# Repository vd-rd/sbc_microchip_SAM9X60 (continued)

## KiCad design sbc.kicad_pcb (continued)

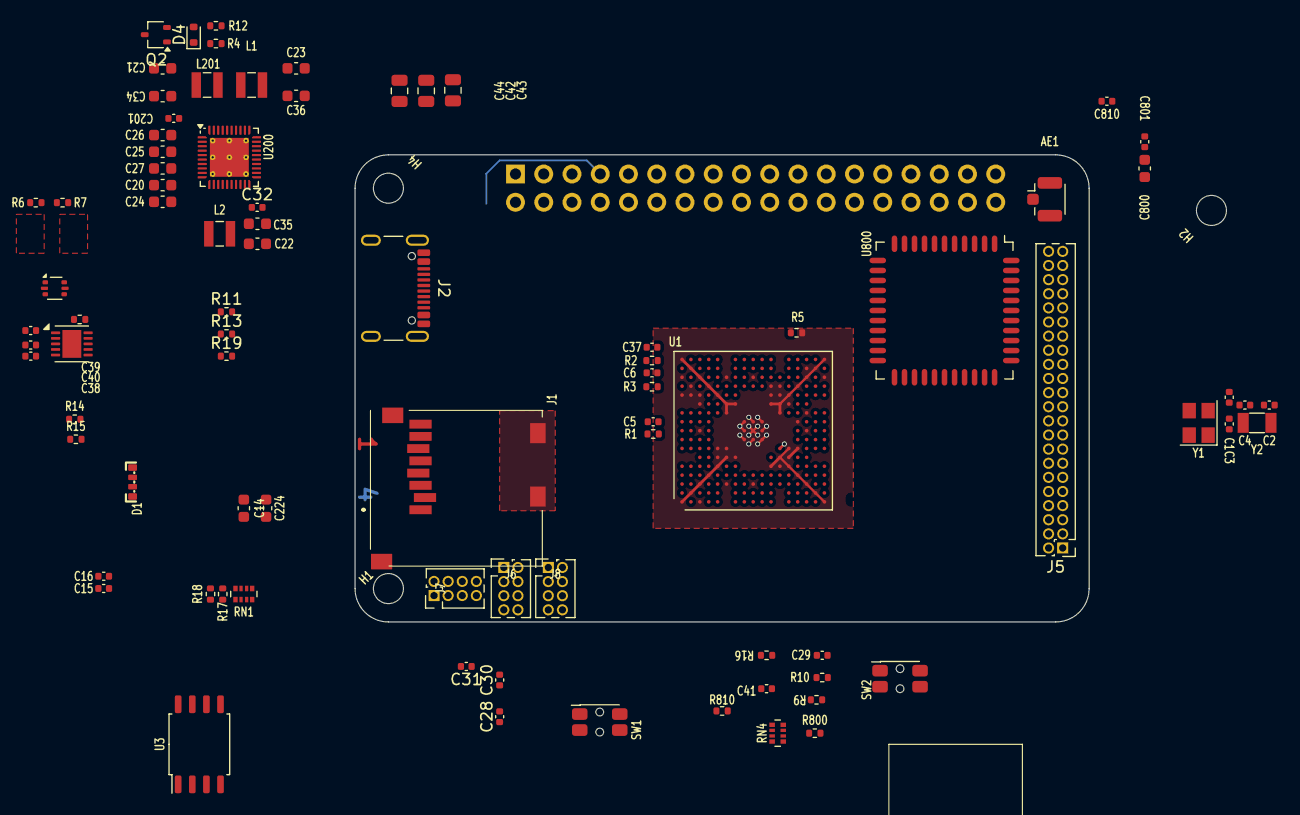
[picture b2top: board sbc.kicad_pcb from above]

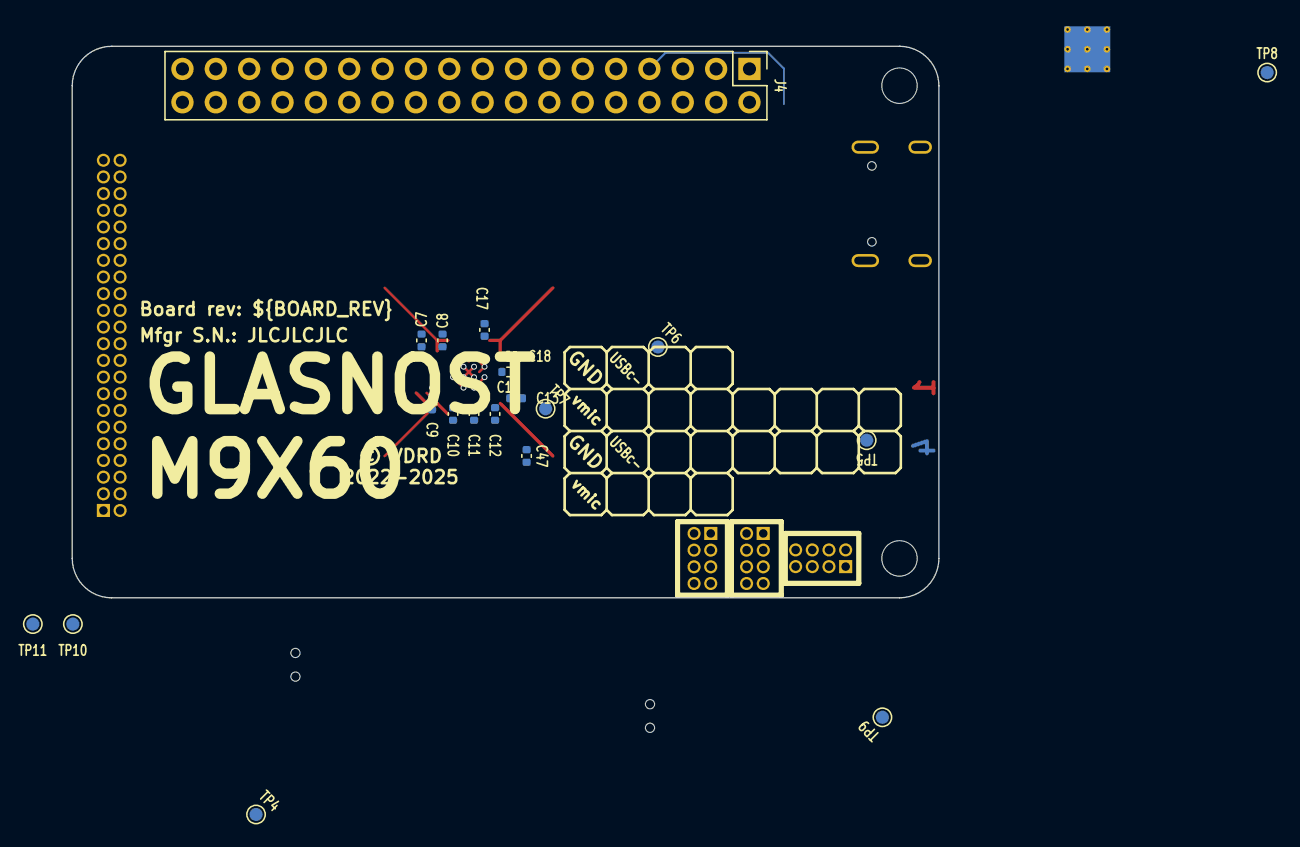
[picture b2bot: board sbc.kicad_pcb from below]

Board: 4 copper layers, 66.0 x 42.0 mm, 107 parts (20 on the bottom side), 124 nets.

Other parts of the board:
C15: 1uF; C_0402_1005Metric
C16: 100nF; C_0402_1005Metric
H1, H2, H4: MountingHole; MountingHole_2.7mm_M2.5_DIN965
J1: Micro_SD_Card_Det; MEM20610118800A
J2: USB_C_Receptacle_USB2.0_16P; USB_C_Receptacle_GCT_USB4105-xx-A_16P_TopMnt_Horizontal
R6: 82k; R_0402_1005Metric
R7, R8: 47k; R_0402_1005Metric
R11: 2.2K; R_0402_1005Metric
R13, R19: 5.1K; R_0402_1005Metric
R17, R18: 10k; R_0402_1005Metric
RN1: 10k; R_Array_Convex_4x0402
U5: USBLC6-2P6; SOT-666

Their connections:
/sdcard/cc1: J2.A5 (CC1), R19.1
/sdcard/cc2: J2.B5 (CC2), R13.1
GND: C15.2, C16.2, J1.G1 (SHIELD), J1.G2 (SHIELD), J1.P6 (VSS), J2.A1 (GND), J2.A12 (GND), J2.B1 (GND), J2.B12 (GND), J2.S1 (SHIELD), R7.2, R11.2, R13.2, R19.2, U5.2 (GND); also elsewhere on the board
SDIO0-CD: J1.CD1 (DET_A), J1.CD2 (DET_B), R17.2; also elsewhere on the board
SDIO0-CLK: J1.P5 (CLK); also elsewhere on the board
SDIO0-CMD: J1.P3 (CMD), RN1.3 (R3.1); also elsewhere on the board
SDIO0-DAT0: J1.P7 (DAT0), RN1.2 (R2.1); also elsewhere on the board
SDIO0-DAT1: J1.P8 (DAT1), RN1.1 (R1.1); also elsewhere on the board
SDIO0-DAT2: J1.P1 (DAT2), R18.2; also elsewhere on the board
SDIO0-DAT3: J1.P2 (DAT3/CD), RN1.4 (R4.1); also elsewhere on the board
USB0-D+: J2.A6 (D+), J2.B6 (D+)
USB0-D-: J2.A7 (D-), J2.B7 (D-)
USBA-D+: U5.4 (I/O2); also elsewhere on the board
USBA-D-: U5.6 (I/O1); also elsewhere on the board
VBUS: J2.A4 (VBUS), J2.A9 (VBUS), J2.B4 (VBUS), J2.B9 (VBUS), R6.1, R11.1, U5.5 (VBUS); also elsewhere on the board
VBUS-SENSE: R6.2, R7.1
VDD_3V3: C15.1, C16.1, J1.P4 (VDD), R8.1, R17.1, R18.1, RN1.5 (R4.2), RN1.6 (R3.2), RN1.7 (R2.2), RN1.8 (R1.2); also elsewhere on the board

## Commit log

2025-12-15 aligned with other boards
2025-12-15 Kicad bringup (#1)
    * add kicad filters in gitignore
    * adding kicad project
    * defined board shape & placement
    * added power rails
    * added io connectors
    * added rmii and usb
2025-12-15 reorg project structure
2026-01-04 small cosmetic fixes
2026-02-03 backport board features
2026-02-05 align board with atsama5d27 board
2026-02-06 finished schematic assignments
2026-02-09 trying out positioning
2026-02-18 schematic fixes
2026-04-20 parts shuffling
2026-05-02 updated gitignore
2026-05-03 routed lcd bus
2026-05-04 nand bus done
2026-05-09 layout optimizations
2026-05-11 try new pmic layout
2026-05-13 propose new layout for pmic
2026-05-25 fix board properties
2026-05-26 update wip board render
2026-06-09 more routing work
2026-06-30 more routing
